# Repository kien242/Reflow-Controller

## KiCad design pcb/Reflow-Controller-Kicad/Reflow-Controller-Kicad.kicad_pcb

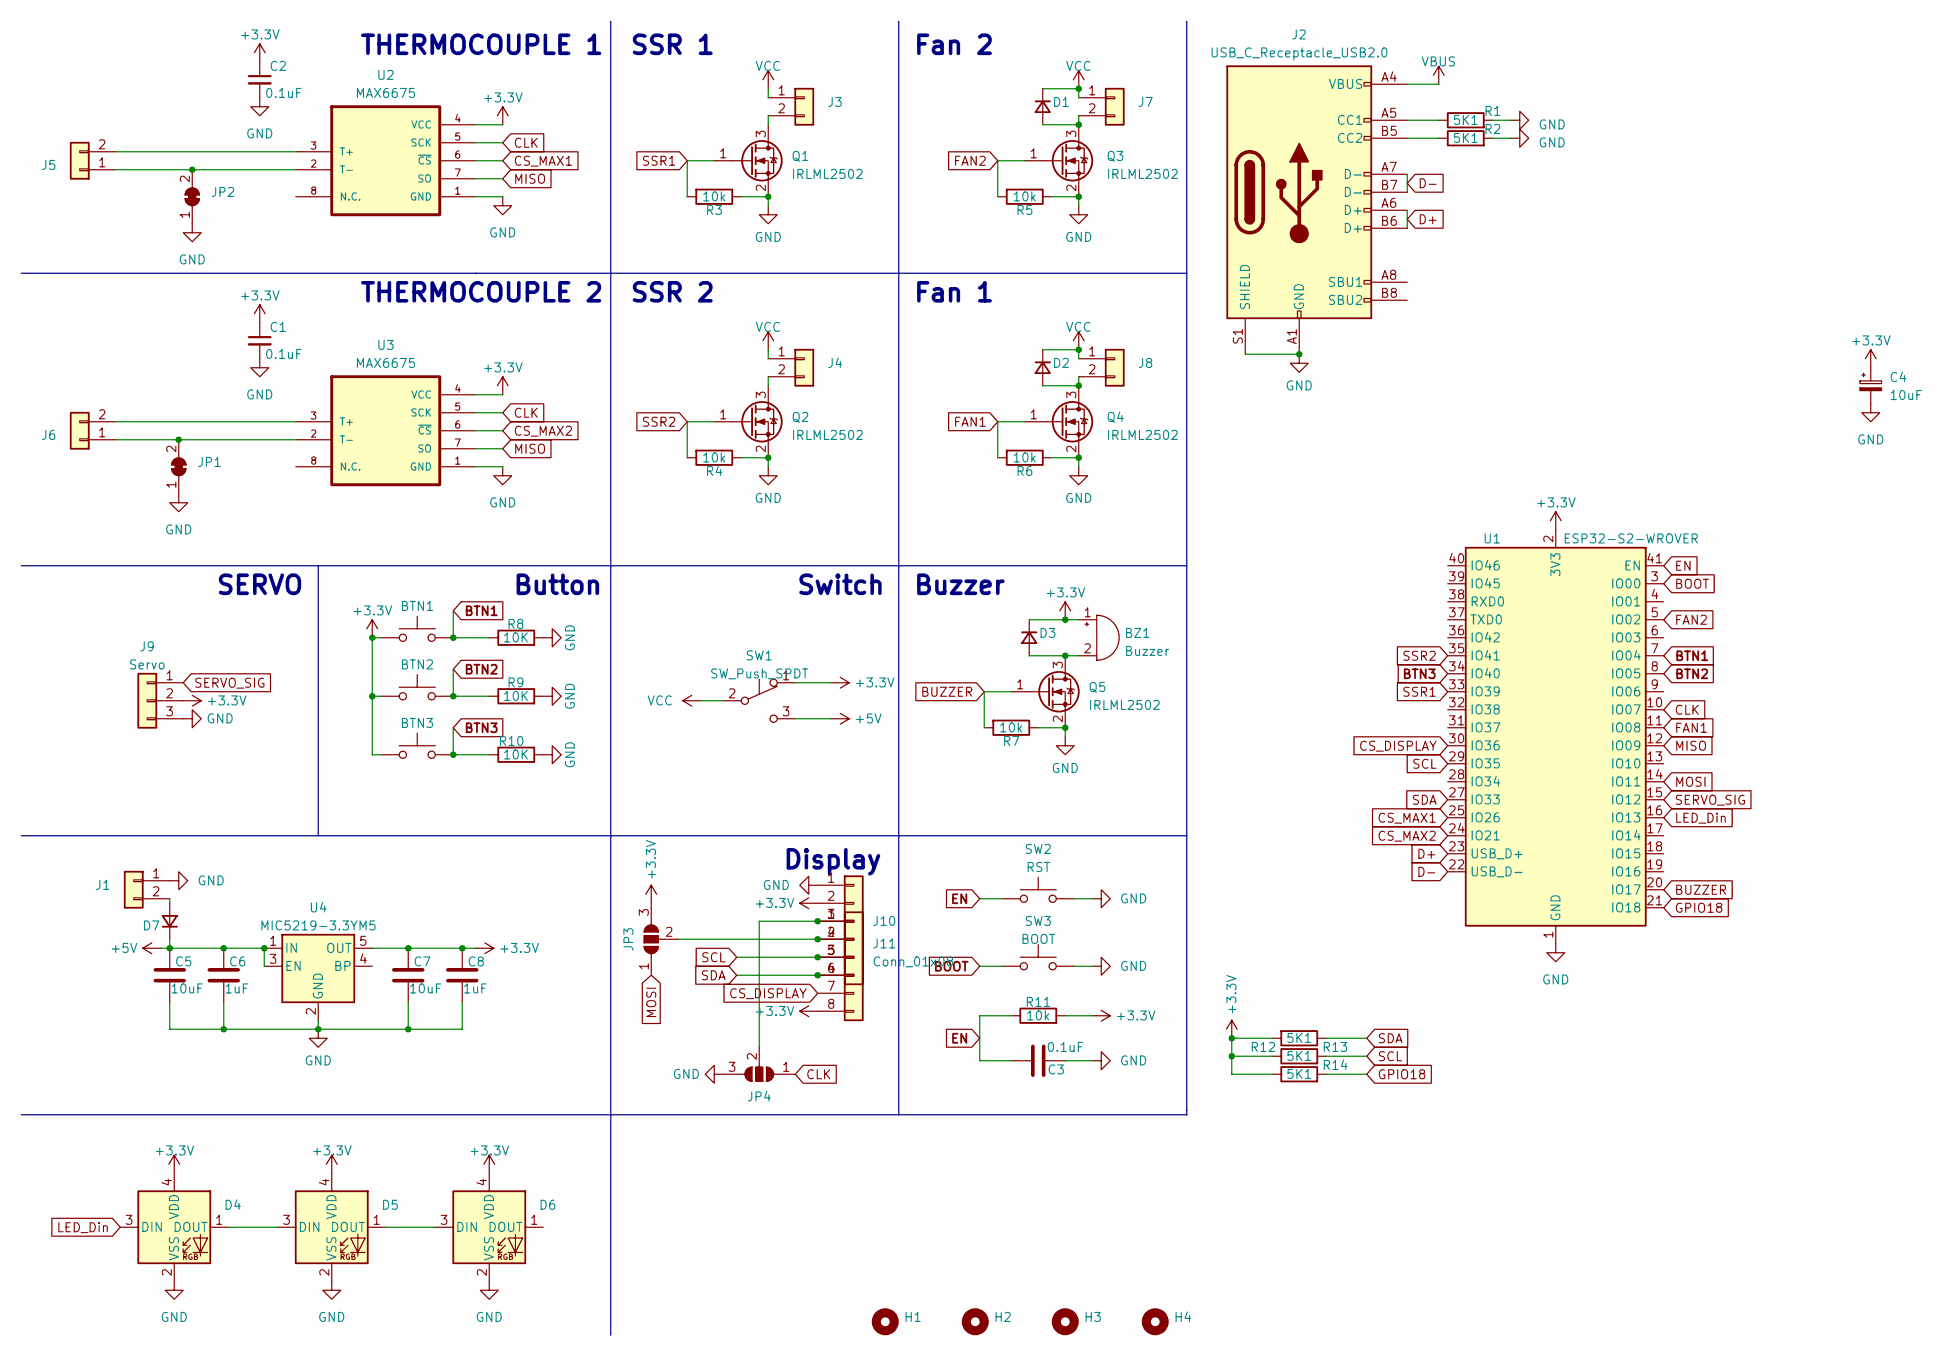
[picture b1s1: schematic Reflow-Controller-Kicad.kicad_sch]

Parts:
BTN1, BTN2, BTN3: SW_TL3305AF160QG
BZ1: Buzzer; MagneticBuzzer_CUI_CMT-8504-100-SMT
C1, C2, C3: 0.1uF; C_0603_1608Metric_Pad1.08x0.95mm_HandSolder
C4: 10uF; CP_EIA-3216-10_Kemet-I_Pad1.58x1.35mm_HandSolder
C5, C7: 10uF; C_0603_1608Metric_Pad1.08x0.95mm_HandSolder
C6, C8: 1uF; C_0603_1608Metric_Pad1.08x0.95mm_HandSolder
D1, D2, D3, D7: D_SOD-123
D4, D5, D6: LED_SK6812MINI_PLCC4_3.5x3.5mm_P1.75mm
H1, H2, H3, H4: MountingHole_2.7mm_M2.5_DIN965_Pad
J1, J3, J4, J5, J6, J7, J8: TerminalBlock_Phoenix_MKDS-1,5-2-5.08_1x02_P5.08mm_Horizont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
J2: USB_C_Receptacle_USB2.0; USB-C-16pin-hight-v2
J9: Servo; TerminalBlock_Phoenix_MKDS-1,5-3-5.08_1x03_P5.08mm_Horizont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
J10: 128x64OLED
J11: Conn_01x08; 0.96_TFT_Display_ST77335S
JP1, JP2: SolderJumper-2_P1.3mm_Open_TrianglePad1.0x1.5mm
JP3, JP4: SolderJumper-3_P2.0mm_Open_TrianglePad1.0x1.5mm
Q1, Q2, Q3, Q4, Q5: IRLML2502; SOT-23_Handsoldering
R1, R2, R12, R13, R14: 5K1; R_0603_1608Metric_Pad0.98x0.95mm_HandSolder
R3, R4, R5, R6, R7, R11: 10k; R_0603_1608Metric_Pad0.98x0.95mm_HandSolder
R8, R9, R10: 10K; R_0603_1608Metric_Pad0.98x0.95mm_HandSolder
SW1: SW_Push_SPDT; MSS22D18
SW2: RST; SW_SPST_B3U-1000P
SW3: BOOT; SW_SPST_B3U-1000P
U1: ESP32-S2-WROVER; MODULE_ESP32-S2-WROVER
U2, U3: MAX6675; SOIC127P600X175-8N
U4: MIC5219-3.3YM5; SOT-23-5_HandSoldering

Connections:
+3.3V: BTN1.1, BTN2.1, BTN3.1, BZ1.1 (-), C1.1, C2.1, C4.1, C7.1, C8.1, D3.1 (K), D4.4 (VDD), D5.4 (VDD), D6.4 (VDD), J9.2, J11.2, J11.8, JP3.3 (B), R11.2, R12.2, R13.1, R14.1, SW1.1 (A), U1.2 (3V3), U2.4 (VCC), U3.4 (VCC), U4.5 (OUT)
+5V: C5.1, C6.1, D7.1 (K), SW1.3 (C), U4.1 (IN), U4.3 (EN)
BOOT: SW3.1, U1.3 (IO00)
BTN1: BTN1.2, R8.1, U1.7 (IO04)
BTN2: BTN2.2, R9.1, U1.8 (IO05)
BTN3: BTN3.2, R10.1, U1.34 (IO40)
BUZZER: Q5.1 (G), R7.2, U1.20 (IO17)
CLK: JP4.1 (A), U1.10 (IO07), U2.5 (SCK), U3.5 (SCK)
CS_DISPLAY: J11.7, U1.30 (IO36)
CS_MAX1: U1.25 (IO26), U2.6 (~CS)
CS_MAX2: U1.24 (IO21), U3.6 (~CS)
D+: J2.A6 (D+), J2.B6 (D+), U1.23 (USB_D+)
D-: J2.A7 (D-), J2.B7 (D-), U1.22 (USB_D-)
EN: C3.1, R11.1, SW2.1, U1.41 (EN)
FAN1: Q4.1 (G), R6.2, U1.11 (IO08)
FAN2: Q3.1 (G), R5.2, U1.5 (IO02)
GND: C1.2, C2.2, C3.2, C4.2, C5.2, C6.2, C7.2, C8.2, D4.2 (VSS), D5.2 (VSS), D6.2 (VSS), J1.1, J2.A1 (GND), J2.A12 (GND), J2.B1 (GND), J2.B12 (GND), J2.S1 (SHIELD), J9.3, J11.1, JP1.1 (A), JP2.1 (A), JP4.3 (B), Q1.2 (S), Q2.2 (S), Q3.2 (S), Q4.2 (S), Q5.2 (S), R1.2, R2.2, R3.1, R4.1, R5.1, R6.1, R7.1, R8.2, R9.2, R10.2, SW2.2, SW3.2, U1.1 (GND), U1.26 (GND), U1.42 (GND), U1.43 (GND), U2.1 (GND), U3.1 (GND), U4.2 (GND)
GPIO18: R14.2, U1.21 (IO18)
LED_Din: D4.3 (DIN), U1.16 (IO13)
MISO: U1.12 (IO09), U2.7 (SO), U3.7 (SO)
MOSI: JP3.1 (A), U1.14 (IO11)
unnamed: BZ1.2 (+), D3.2 (A), Q5.3 (D)
unnamed: D1.2 (A), J7.2, Q3.3 (D)
unnamed: D2.2 (A), J8.2, Q4.3 (D)
unnamed: D4.1 (DOUT), D5.3 (DIN)
unnamed: D5.1 (DOUT), D6.3 (DIN)
unnamed: D7.2 (A), J1.2
unnamed: J2.A5 (CC1), R1.1
unnamed: J2.B5 (CC2), R2.1
unnamed: J3.2, Q1.3 (D)
unnamed: J4.2, Q2.3 (D)
unnamed: J5.1, JP2.2 (B), U2.2 (T-)
unnamed: J5.2, U2.3 (T+)
unnamed: J6.1, JP1.2 (B), U3.2 (T-)
unnamed: J6.2, U3.3 (T+)
unnamed: J10.1, J11.3, JP4.2 (C)
unnamed: J10.2, J11.4, JP3.2 (C)
SCL: J10.3, J11.5, R13.2, U1.29 (IO35)
SDA: J10.4, J11.6, R12.1, U1.27 (IO33)
SERVO_SIG: J9.1, U1.15 (IO12)
SSR1: Q1.1 (G), R3.2, U1.33 (IO39)
SSR2: Q2.1 (G), R4.2, U1.35 (IO41)
VBUS: J2.A4 (VBUS), J2.A9 (VBUS), J2.B4 (VBUS), J2.B9 (VBUS)
VCC: D1.1 (K), D2.1 (K), J3.1, J4.1, J7.1, J8.1, SW1.2 (B)

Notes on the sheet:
Button
THERMOCOUPLE 1
Fan 2
Display
SERVO
Fan 1
SSR 1
Switch
Buzzer
SSR 2
THERMOCOUPLE 2

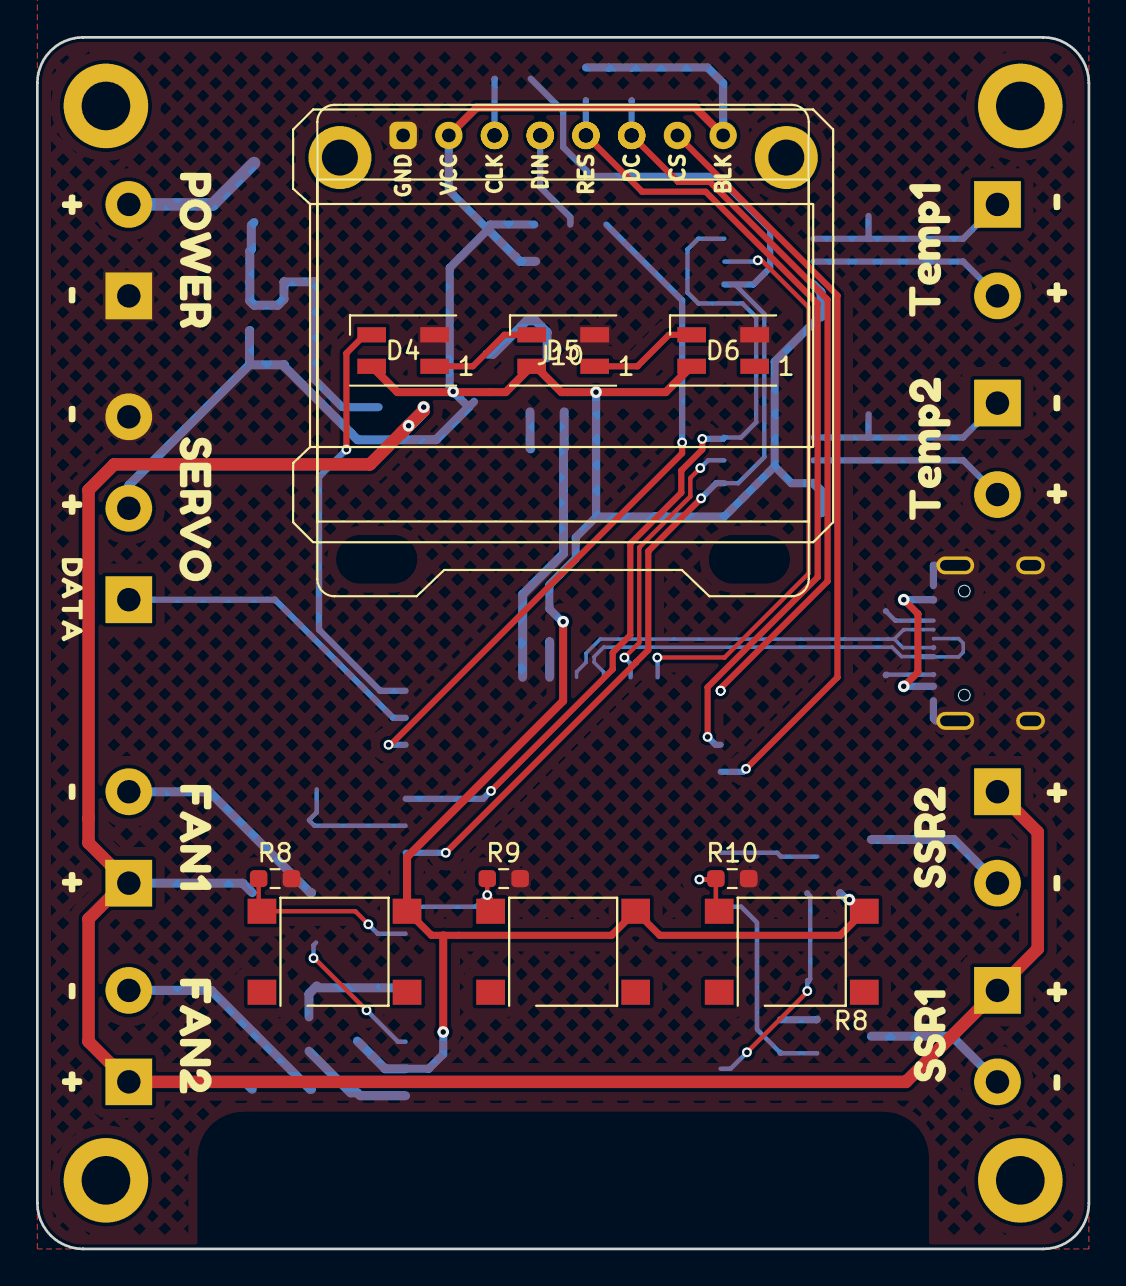
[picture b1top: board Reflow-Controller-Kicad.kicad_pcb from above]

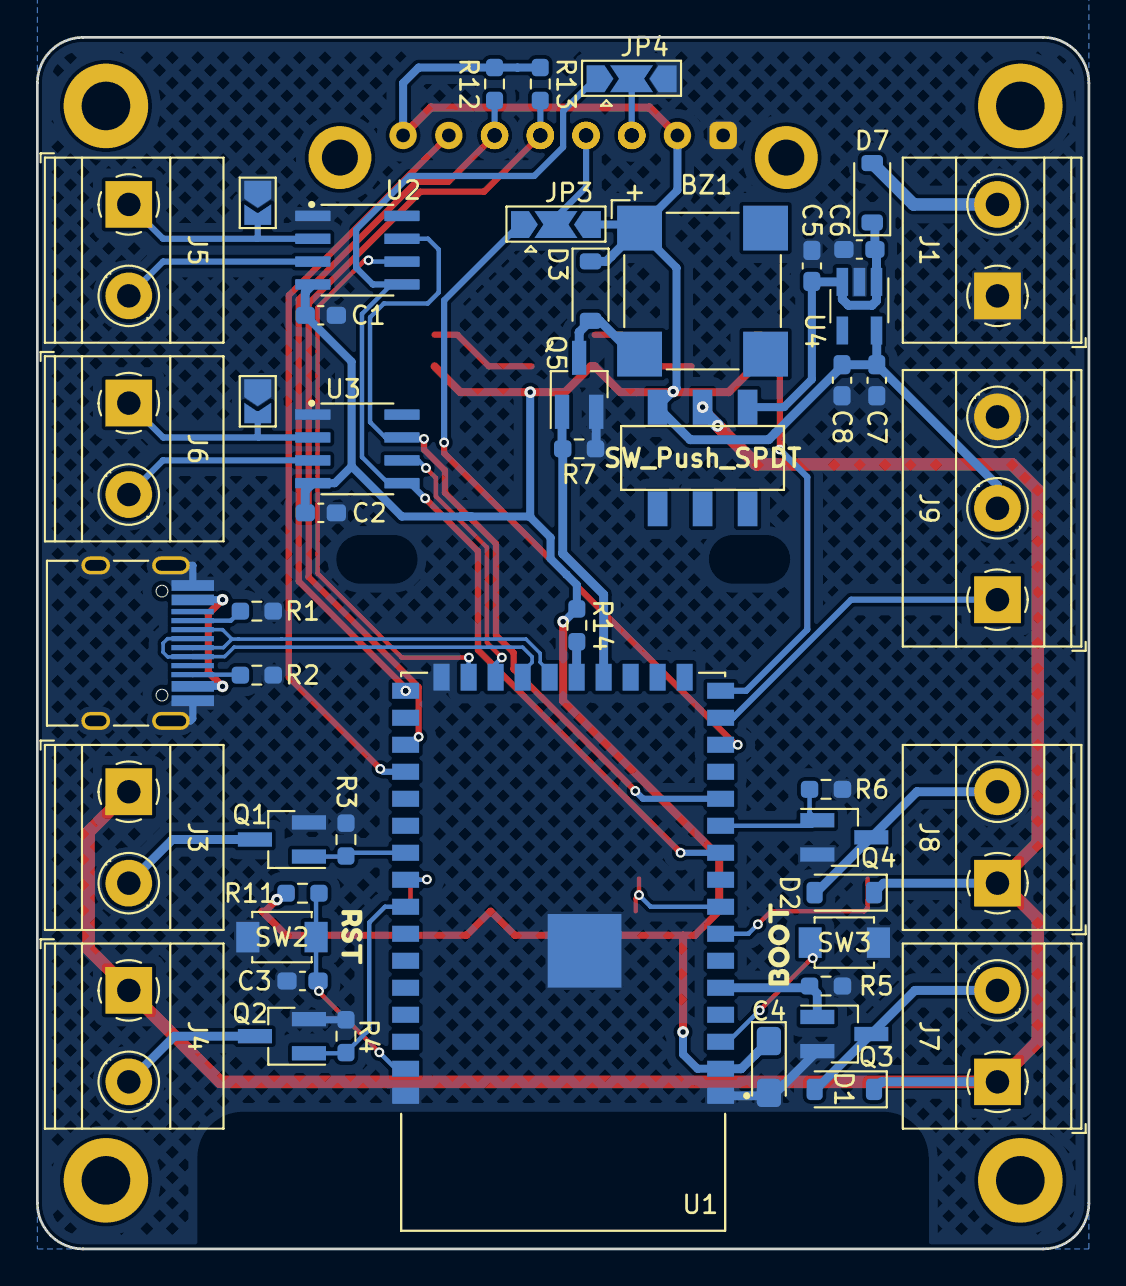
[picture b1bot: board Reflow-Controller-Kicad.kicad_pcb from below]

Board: 2 copper layers, 58.4 x 67.3 mm, 91 parts (51 on the bottom side), 44 nets.

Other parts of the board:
kibuzzard-643A05B4: G***; kibuzzard-643A05B4
kibuzzard-643A05BD, kibuzzard-643A05BD#2, kibuzzard-643A05BD#3, kibuzzard-643A05BD#4, kibuzzard-643A05BD#5, kibuzzard-643A05BD#6, kibuzzard-643A05BD#7, kibuzzard-643A05BD#8: G***; kibuzzard-643A05BD
kibuzzard-643A05CF, kibuzzard-643A05CF#2, kibuzzard-643A05CF#3, kibuzzard-643A05CF#4, kibuzzard-643A05CF#5, kibuzzard-643A05CF#6, kibuzzard-643A05CF#7, kibuzzard-643A05CF#8: G***; kibuzzard-643A05CF
kibuzzard-643A09AD: G***; kibuzzard-643A09AD
kibuzzard-643A051C: G***; kibuzzard-643A051C
kibuzzard-643A052F: G***; kibuzzard-643A052F
kibuzzard-643A059F: G***; kibuzzard-643A059F
kibuzzard-643A0514: G***; kibuzzard-643A0514
kibuzzard-643A0524: G***; kibuzzard-643A0524
kibuzzard-643A0580: G***; kibuzzard-643A0580
kibuzzard-643A0588: G***; kibuzzard-643A0588
kibuzzard-643A0606: G***; kibuzzard-643A0606
kibuzzard-643A0998: G***; kibuzzard-643A0998

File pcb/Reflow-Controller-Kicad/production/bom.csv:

Designator,Footprint,Quantity,Value,LCSC Part #
"BTN1, BTN2, BTN3",SW_TL3305AF160QG,3, ,
BZ1,MagneticBuzzer_CUI_CMT-8504-100-SMT,1,Buzzer,
"C1, C2, C3",0603,3,0.1uF,
C4,CP_EIA-3216-10_Kemet-I_Pad1.58x1.35mm_HandSolder,1,10uF,
"C5, C7",0603,2,10uF,
"C6, C8",0603,2,1uF,
"D1, D2, D3, D7",D_SOD-123,4, ,
"D4, D5, D6",LED_SK6812MINI_PLCC4_3.5x3.5mm_P1.75mm,3, ,
"H1, H2, H3, H4",MountingHole_2.7mm_M2.5_DIN965_Pad,4, ,
"J1, J3, J4, J5, J6, J7, J8","TerminalBlock_Phoenix_MKDS-1,5-2-5.08_1x02_P5.08mm_Horizontal",7, ,
J10,128x64OLED,1, ,
J11,0.96_TFT_Display_ST77335S,1,Conn_01x08,
J2,USB-C-16pin-hight-v2,1,USB_C_Receptacle_USB2.0,
J9,"TerminalBlock_Phoenix_MKDS-1,5-3-5.08_1x03_P5.08mm_Horizontal",1,Servo ,
"JP1, JP2",SolderJumper-2_P1.3mm_Open_TrianglePad1.0x1.5mm,2, ,
"JP3, JP4",SolderJumper-3_P2.0mm_Open_TrianglePad1.0x1.5mm,2, ,
"Q1, Q2, Q3, Q4, Q5",SOT-23_Handsoldering,5,IRLML2502,
"R1, R12, R13, R14, R2",0603,5,5K1,
"R10, R11, R3, R4, R5, R6, R7, R8, R9",0603,9,10K,
SW1,MSS22D18,1,SW_Push_SPDT,
SW2,SW_SPST_B3U-1000P,1,RST,
SW3,SW_SPST_B3U-1000P,1,BOOT,
U1,MODULE_ESP32-S2-WROVER,1,ESP32-S2-WROVER,
"U2, U3",SOIC127P600X175-8N,2,MAX6675,
U4,SOT-23-5_HandSoldering,1,MIC5219-3.3YM5,

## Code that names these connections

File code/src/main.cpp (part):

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#define SDA_PIN         33
#define SCL_PIN         35
#define OLED_RST_PIN    45
#define CS_MAX1_PIN     13
#define CS_MAX2_PIN     12
#define MISO_PIN        9
#define MOSI_PIN        11
#define CLK_PIN         7

#define MOS_CTRL1_PIN   5
#define MOS_CTRL2_PIN   6
#define SSR1_PIN        1
#define SSR2_PIN        2
#define SERVO_PIN       3
#define BUZZER_PIN      15
#define BTN1_PIN        36
#define BTN2_PIN        39
#define BTN3_PIN        40


#define LED_PIN         37
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const int PWMResolution = 10;                       //12 bits 0-4095


MAX6675 thermocouple1(CLK_PIN, CS_MAX2_PIN, MISO_PIN);
MAX6675 thermocouple2(CLK_PIN, CS_MAX1_PIN, MISO_PIN);

float current_temperature1 = 0.0;
float current_temperature2 = 0.0;
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  Serial.begin(115200);
  Serial.println("start");

  pinMode(BTN1_PIN, INPUT);
  pinMode(BTN2_PIN, INPUT);
  pinMode(BTN3_PIN, INPUT);

  pinMode(CS_MAX1_PIN, OUTPUT);
  pinMode(CS_MAX2_PIN, OUTPUT);
  digitalWrite(CS_MAX1_PIN, LOW);
  digitalWrite(CS_MAX2_PIN, LOW);

  pinMode(SSR1_PIN, OUTPUT);
  pinMode(SSR2_PIN, OUTPUT);
  digitalWrite(SSR1_PIN, LOW);
  digitalWrite(SSR2_PIN, LOW);

  delay(100);
  FastLED.addLeds<NEOPIXEL, LED_PIN>(leds, NUM_LEDS);
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  leds[0] = CRGB::Black;
  FastLED.show();

  pinMode(BUZZER_PIN, OUTPUT);
  digitalWrite(BUZZER_PIN, LOW);

  ledcSetup(PWMChannel, PWMFreq, PWMResolution);
  ledcAttachPin(BUZZER_PIN, PWMChannel);
  ledcWrite(PWMChannel, dutyCycle);

  ledcWrite(PWMChannel, 500);
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unsigned long t_reflow_finish = millis() + 900;

void loop() {
  if(digitalRead(BTN1_PIN) == 1){
    leds[0] = CRGB::Blue;
    FastLED.show();
    delay(50);
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    int wait_time_increase = 300;
    bool set_process = false;

    while (digitalRead(BTN1_PIN) == 1){
      if(millis() >= t_btn_pressed + wait_time_increase && !set_process){
        wait_time_increase = 80;
        t_btn_pressed = millis();
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    leds[0] = CRGB::Black;
    FastLED.show();
  }
  else if(digitalRead(BTN2_PIN) == 1){
    leds[0] = CRGB::Blue;
    FastLED.show();
    delay(50);
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    int wait_time_increase = 300;
    bool set_process = false;
    
    while (digitalRead(BTN2_PIN) == 1){
      if(millis() >= t_btn_pressed + wait_time_increase && !set_process){
        leds[0] = CRGB::Orange;
        FastLED.show();
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    leds[0] = CRGB::Black;
    FastLED.show();
  }
  else if(digitalRead(BTN3_PIN) == 1){
    leds[0] = CRGB::Blue;
    FastLED.show();
    delay(50);
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    update_display();

    unsigned long t_btn_pressed = millis();
    while (digitalRead(BTN3_PIN) == 1){
      if(millis() >= t_btn_pressed + 800){
        leds[0] = CRGB::Orange;
        FastLED.show();
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    }
    else{
      msg2display_bot = "";
      digitalWrite(SSR1_PIN, LOW);
      leds[0] = CRGB::Black;
      FastLED.show();
    }
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    if(current_temperature1 < 30){
      if(millis() >= t_reflow_control + 500){
        t_reflow_control = millis();
        digitalWrite(SSR1_PIN, !digitalRead(SSR1_PIN));
        leds[0] = digitalRead(SSR1_PIN) ? CRGB::Blue : CRGB::Yellow; 
        FastLED.show();
        t_pid_on = millis();
      }
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      update_display();
    }

    if(digitalRead(BTN1_PIN) == 1 || digitalRead(BTN2_PIN) == 1 || digitalRead(BTN3_PIN) == 1){
      reflow_done = false;
      ledcWrite(PWMChannel, 0);
      leds[0] = CRGB::Black; 
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      profile_counter = 0;
      pid_setpoint = temp_reflow_individual[0];
      
      while(digitalRead(BTN1_PIN) == 1 || digitalRead(BTN2_PIN) == 1 || digitalRead(BTN3_PIN) == 1){ 
        delay(100); 
      }
    }
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      t_reflow_control = millis();
      
      if(pid_output > 50){
        digitalWrite(SSR1_PIN, HIGH);
        leds[0] = CRGB::Red;
        FastLED.show();
        t_pid_on = millis();
      }
    }

    if(millis() > t_pid_on + pid_output && digitalRead(SSR1_PIN)){
      digitalWrite(SSR1_PIN, LOW);
      leds[0] = CRGB::Yellow;
      FastLED.show();
    }
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        running_reflow = false;
        t_reflow_finish = millis();
        reflow_done = true;
        digitalWrite(SSR1_PIN, LOW);
        leds[0] = CRGB::Yellow;
        FastLED.show();
      }
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    }
    else{
      msg2display_bot = "";
      digitalWrite(SSR1_PIN, LOW);
      leds[0] = CRGB::Black;
      FastLED.show();
    }
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      }
      
      if(pid_output > 50){
        digitalWrite(SSR1_PIN, HIGH);
        leds[0] = CRGB::Red;
        FastLED.show();
        t_pid_on = millis();
      }
    }

    if(millis() > t_pid_on + pid_output && digitalRead(SSR1_PIN)){
      digitalWrite(SSR1_PIN, LOW);
      leds[0] = CRGB::Yellow;
      FastLED.show();
    }
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
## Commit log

2023-04-16 add my PCB
